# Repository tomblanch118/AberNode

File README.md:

# AberNode
Documents, designs, schematics, board layouts, BOMs, code and all materials for the AberNodes

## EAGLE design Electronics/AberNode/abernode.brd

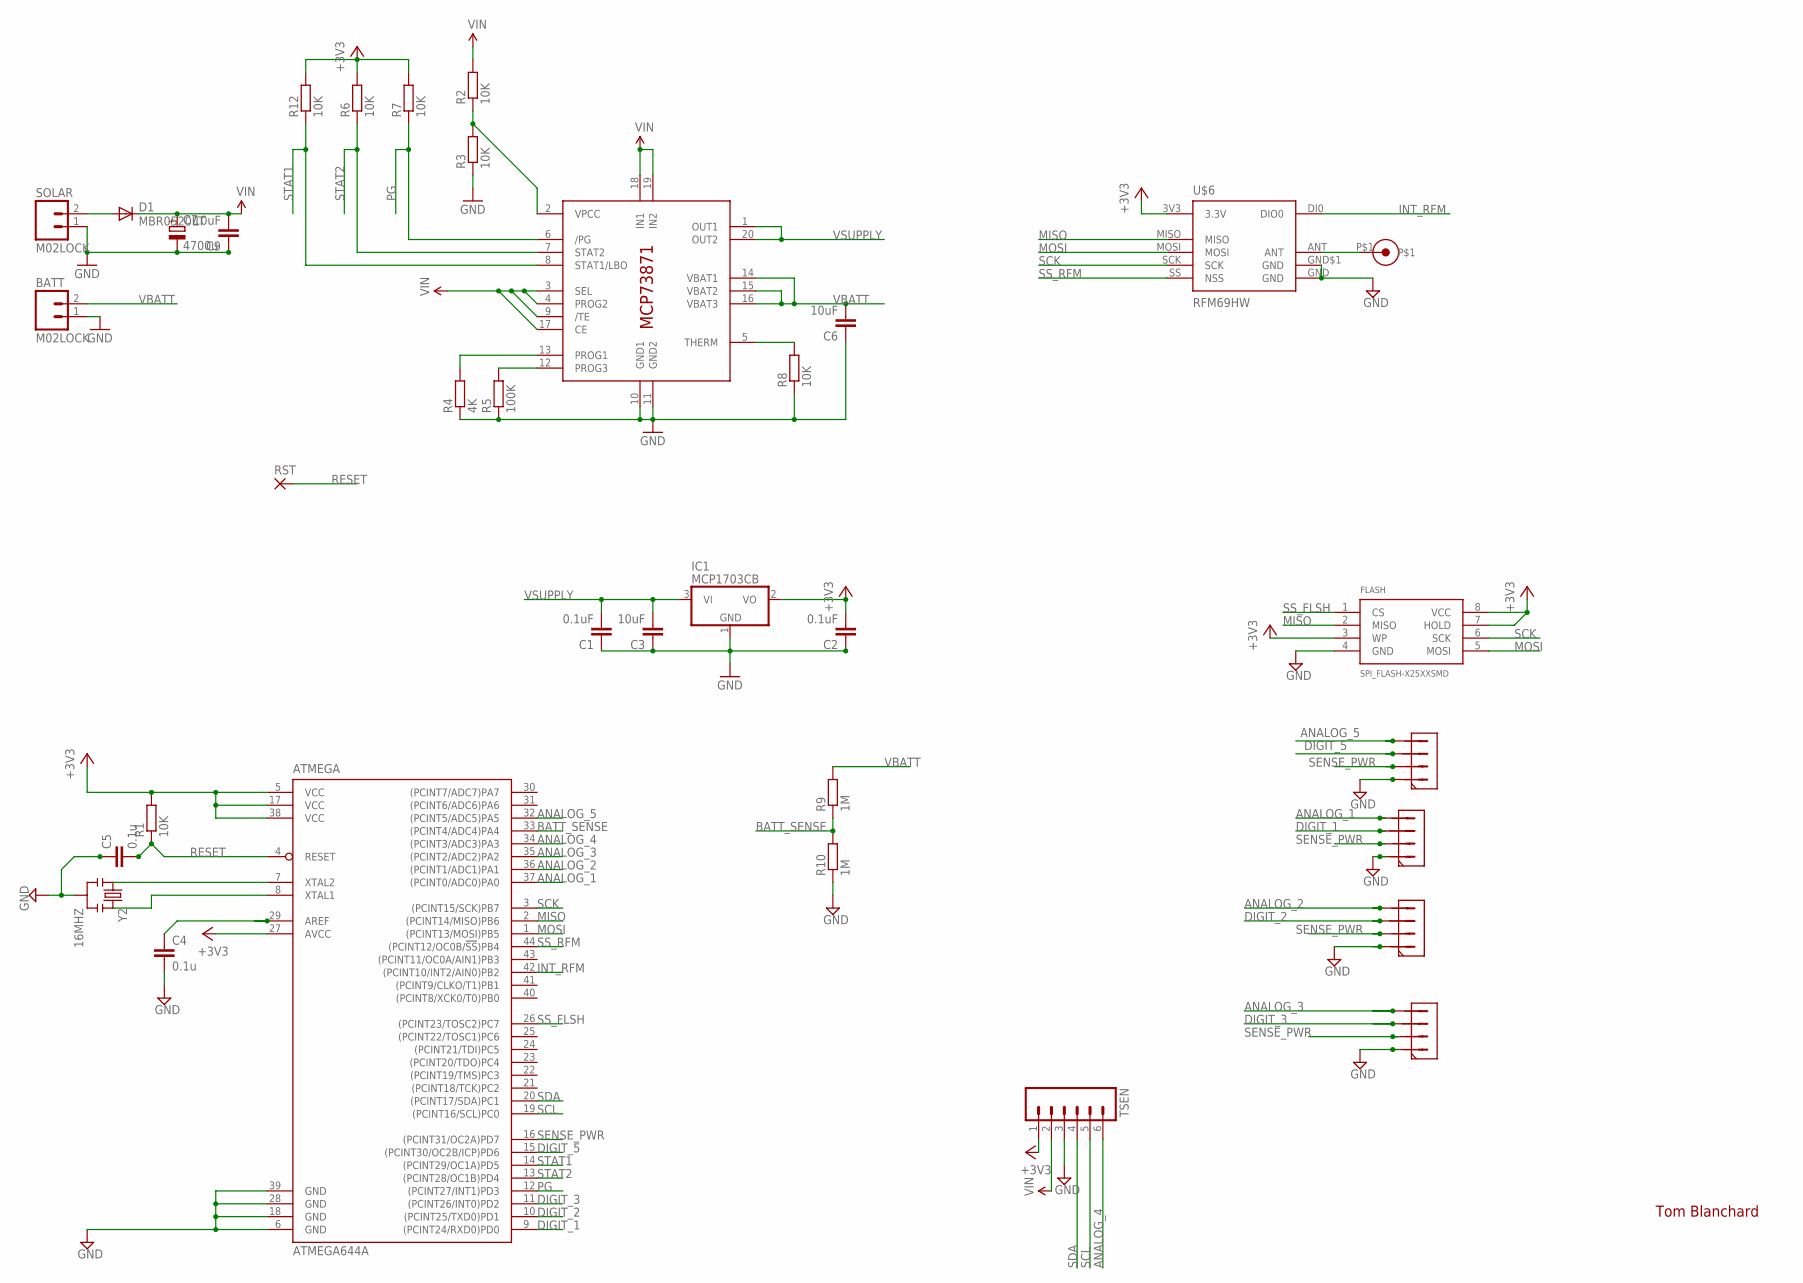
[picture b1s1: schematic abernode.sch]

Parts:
ATMEGA: ATMEGA644A; TQFP44
BATT: M02LOCK; 1X02_LOCK
C1, C2: 0.1uF; C0603
C3, C6, C9: 10uF; C0805
C4, C5: 0.1u; C0603
C7: 4700u; E7,5-18
D1: MBR0520LT; SOD123
FLASH: SPI_FLASH-X25XXSMD; SO08
IC1: MCP1703CB; SOT23
IC2: MCP73871; QFN20
R1, R2, R3, R6, R7, R8, R12: 10K; R0603
R4: 4K; R0603
R5: 100K; R0603
R9, R10: 1M; R0603
RST: SMD2; SMD1,27-2,54
SEN1, SEN2, SEN3, SEN4: HEADER_4
SOLAR: M02LOCK; 1X02_LOCK
TSEN: M06LONGPADS; 1X06_LONGPADS
U$6: RFM69HW; RFM69W-XXXS2
U$7: ANT
Y2: 16MHZ; RESONATOR-SMD

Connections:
+3V3: ATMEGA.5 (VCC), ATMEGA.17 (VCC), ATMEGA.27 (AVCC), ATMEGA.38 (VCC), C2.2, FLASH.3 (WP), FLASH.7 (HOLD), FLASH.8 (VCC), IC1.2 (VO), R1.2, R6.2, R7.2, R12.2, TSEN.1, U$6.3V3 (3.3V)
ANALOG_1: ATMEGA.37 ((PCINT0/ADC0)PA0), SEN2.4
ANALOG_2: ATMEGA.36 ((PCINT1/ADC1)PA1), SEN1.4
ANALOG_3: ATMEGA.35 ((PCINT2/ADC2)PA2), SEN4.4
ANALOG_4: ATMEGA.34 ((PCINT3/ADC3)PA3), TSEN.6
ANALOG_5: ATMEGA.32 ((PCINT5/ADC5)PA5), SEN3.4
BATT_SENSE: ATMEGA.33 ((PCINT4/ADC4)PA4), R9.1, R10.2
DIGIT_1: ATMEGA.9 ((PCINT24/RXD0)PD0), SEN2.3
DIGIT_2: ATMEGA.10 ((PCINT25/TXD0)PD1), SEN1.3
DIGIT_3: ATMEGA.11 ((PCINT26/INT0)PD2), SEN4.3
DIGIT_5: ATMEGA.15 ((PCINT30/OC2B/ICP)PD6), SEN3.3
GND: ATMEGA.6 (GND), ATMEGA.18 (GND), ATMEGA.28 (GND), ATMEGA.39 (GND), BATT.1, C1.1, C2.1, C3.1, C4.2, C5.1, C6.1, C7.-, C9.1, FLASH.4 (GND), IC1.1 (GND), IC2.10 (GND1), IC2.11 (GND2), R3.1, R4.1, R5.1, R8.1, R10.1, SEN1.1, SEN2.1, SEN3.1, SEN4.1, SOLAR.1, TSEN.3, U$6.GND, U$6.GND$1 (GND), Y2.2
INT_RFM: ATMEGA.42 ((PCINT10/INT2/AIN0)PB2), U$6.DI0 (DIO0)
MISO: ATMEGA.2 ((PCINT14/MISO)PB6), FLASH.2 (MISO), U$6.MISO
MOSI: ATMEGA.1 ((PCINT13/MOSI)PB5), FLASH.5 (MOSI), U$6.MOSI
unnamed: ATMEGA.8 (XTAL1), Y2.3
unnamed: ATMEGA.7 (XTAL2), Y2.1
unnamed: ATMEGA.29 (AREF), C4.1
unnamed: IC2.12 (PROG3), R5.2
unnamed: IC2.2 (VPCC), R2.1, R3.2
unnamed: IC2.13 (PROG1), R4.2
unnamed: U$6.ANT, U$7.P$1
unnamed: D1.A, SOLAR.2
unnamed: IC2.5 (THERM), R8.2
PG: ATMEGA.12 ((PCINT27/INT1)PD3), IC2.6 (/PG), R7.1
RESET: ATMEGA.4 (RESET), C5.2, R1.1, RST.1
SCK: ATMEGA.3 ((PCINT15/SCK)PB7), FLASH.6 (SCK), U$6.SCK
SCL: ATMEGA.19 ((PCINT16/SCL)PC0), TSEN.5
SDA: ATMEGA.20 ((PCINT17/SDA)PC1), TSEN.4
SENSE_PWR: ATMEGA.16 ((PCINT31/OC2A)PD7), SEN1.2, SEN2.2, SEN3.2, SEN4.2
SS_FLSH: ATMEGA.26 ((PCINT23/TOSC2)PC7), FLASH.1 (CS)
SS_RFM: ATMEGA.44 ((PCINT12/OC0B/!SS!)PB4), U$6.SS (NSS)
STAT1: ATMEGA.14 ((PCINT29/OC1A)PD5), IC2.8 (STAT1/LBO), R12.1
STAT2: ATMEGA.13 ((PCINT28/OC1B)PD4), IC2.7 (STAT2), R6.1
VBATT: BATT.2, C6.2, IC2.14 (VBAT1), IC2.15 (VBAT2), IC2.16 (VBAT3), R9.2
VIN: C7.+, C9.2, D1.C, IC2.3 (SEL), IC2.4 (PROG2), IC2.9 (/TE), IC2.17 (CE), IC2.18 (IN1), IC2.19 (IN2), R2.2, TSEN.2
VSUPPLY: C1.2, C3.2, IC1.3 (VI), IC2.1 (OUT1), IC2.20 (OUT2)

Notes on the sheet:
Tom Blanchard

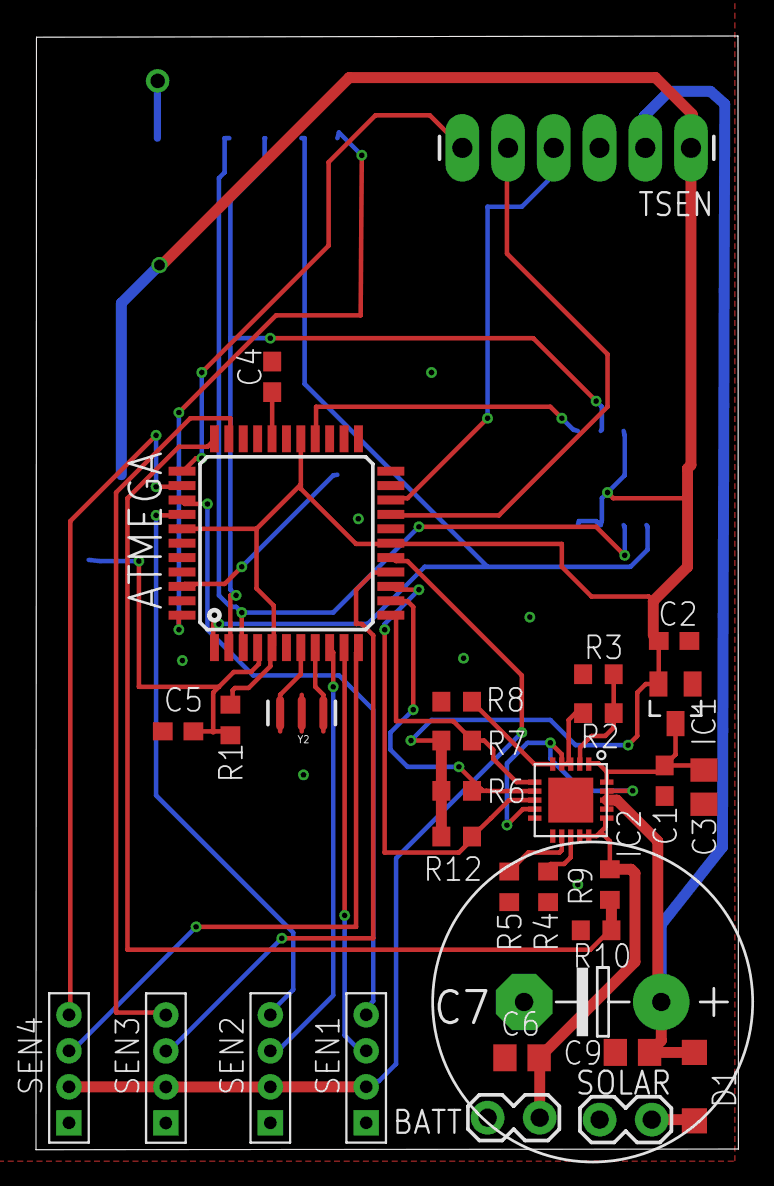
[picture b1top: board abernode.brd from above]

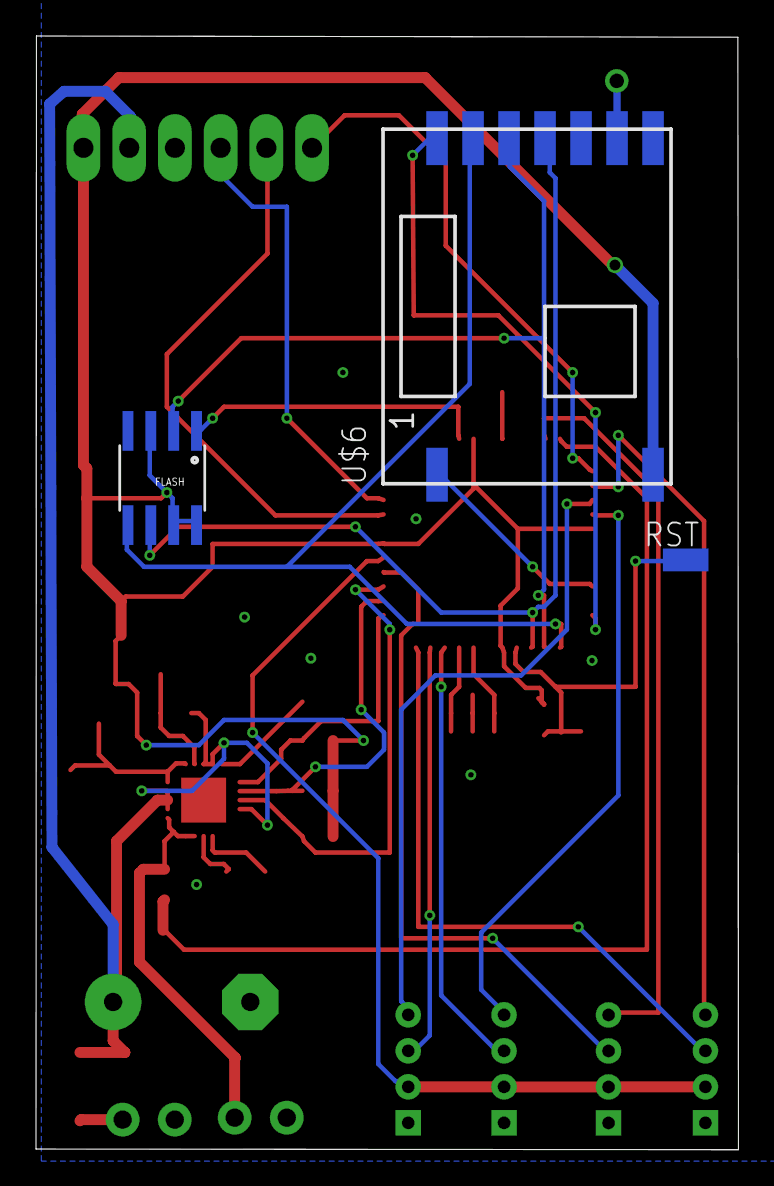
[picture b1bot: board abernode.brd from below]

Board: 2 copper layers, 39.0 x 61.9 mm, 35 parts (3 on the bottom side), 37 nets.

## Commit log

2016-01-12 Initial structure commit
2016-01-14 Schematic Mostly Done
2016-01-21 Board Designed minus res values
    Need to sort out the resistor values for the mcp73871 pullups battery
    sense and charging rates.
2016-01-27 Board redesign
    Moved components around, changed orientation of connectors. Added extra
    sensor connector. Power to bottom sensor connectors is driven from a
    iopin to reduce current draw whilst sleeping.
2016-01-29 Mostly Done
    Routed power to connectors through io pin, added reset pad for
    programming.
2016-02-01 First Production Version
2016-04-18 Added simple but stable code for node and basestation

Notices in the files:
parts and their libraries:
SparkFun-DigitalIC: Licensing: Creative Commons ShareAlike 4.0 International - https://creativecommons.org/licenses/by-sa/4.0
